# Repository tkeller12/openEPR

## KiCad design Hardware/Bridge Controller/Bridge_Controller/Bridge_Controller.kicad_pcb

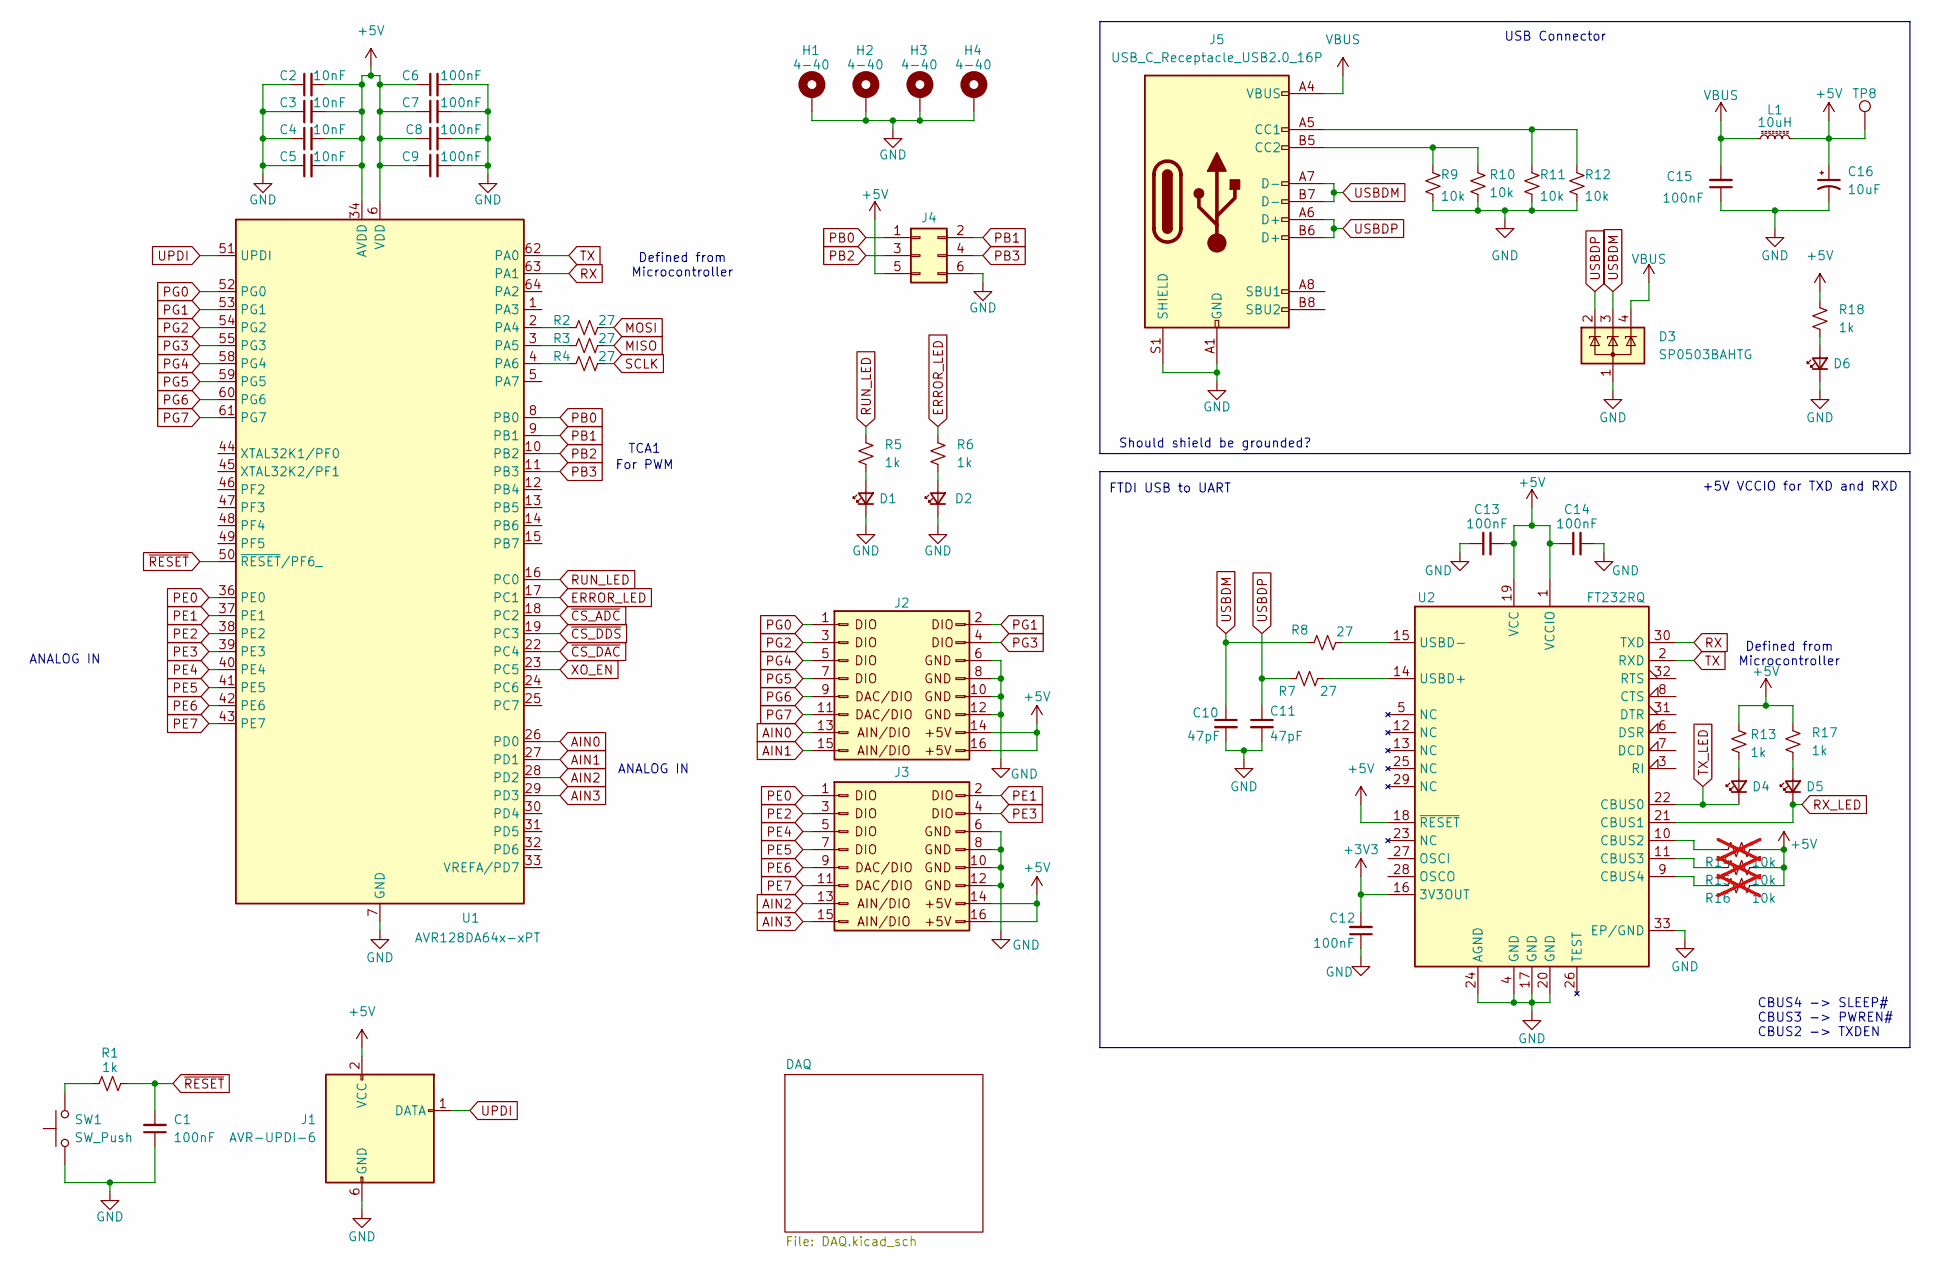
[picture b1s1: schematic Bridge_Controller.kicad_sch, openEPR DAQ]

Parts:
C1, C6, C7, C8, C9, C12, C13, C14, C15: 100nF; C_0603_1608Metric; Digikey 490-4779-1-ND
C2, C3, C4, C5: 10nF; C_0603_1608Metric; Digikey 490-4778-1-ND
C10, C11: 47pF; C_0603_1608Metric; Digikey 490-4944-1-ND
C16: 10uF; CP_EIA-3216-18_Kemet-A; Digikey 399-3684-1-ND
D1, D4, D5, D6: 150080VS75000; LED_0805_2012Metric; Digikey 732-4986-1-ND
D2: 150080SS75000; LED_0805_2012Metric; Digikey 732-4985-1-ND
D3: SP0503BAHTG; SOT-143; Digikey F2715CT-ND
H1, H2, H3, H4: 4-40; 4-40_Hole_Pad
J1: AVR-UPDI-6; PinHeader_2x03_P2.54mm_Vertical; Digikey 609-3234-ND
J2, J3: Conn_02x08_standard_header_for_IO; IDC-Header_2x08_P2.54mm_Vertical; Digikey 900-0702461602-ND
J4: PWM; PinHeader_2x03_P2.54mm_Vertical; Digikey 609-3234-ND
J5: USB_C_Receptacle_USB2.0_16P; USB_C_Receptacle_GCT_USB4085; Digikey 2073-USB4085-GF-ACT-ND
L1: 10uH; L_0805_2012Metric; Digikey 445-6762-1-ND
R1, R5, R6, R13, R17, R18: 1k; R_0603_1608Metric; Digikey 311-1.00KHRCT-ND
R2, R3, R4, R7, R8: 27; R_0603_1608Metric; Digikey 311-27GRCT-ND
R9, R10, R11, R12: 10k; R_0603_1608Metric; Digikey 311-10.0KHRCT-ND
R14, R15, R16: 10k; R_0603_1608Metric; Digikey 311-10.0KHRCT-ND; not fitted
SW1: SW_Push; SW_SPST_B3SL-1002P; Digikey SW1203CT-ND
TP8: TestPoint; TestPoint_Pad_D1.0mm
U1: AVR128DA64x-xPT; TQFP-64_10x10mm_P0.5mm; Digikey 150-AVR128DA64T-I/PTCT-ND
U2: FT232RQ; QFN-32-1EP_5x5mm_P0.5mm_EP3.1x3.1mm; Digikey 768-1307-ND

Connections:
+3V3: C12.2, U2.16 (3V3OUT)
+5V: C2.2, C3.2, C4.2, C5.2, C6.1, C7.1, C8.1, C9.1, C13.2, C14.1, C16.1, J1.2 (VCC), J2.14, J2.16, J3.14, J3.16, J4.5, L1.2, R13.1, R14.2, R15.2, R16.2, R17.1, R18.1, TP8.1, U1.6 (VDD), U1.20 (VDD), U1.34 (AVDD), U1.56 (VDD), U2.1 (VCCIO), U2.18 (~RESET), U2.19 (VCC); also elsewhere on the board
AIN0: J2.13, U1.26 (PD0)
AIN1: J2.15, U1.27 (PD1)
AIN2: J3.13, U1.28 (PD2)
AIN3: J3.15, U1.29 (PD3)
ERROR_LED: R6.1, U1.17 (PC1)
GND: C1.1, C2.1, C3.1, C4.1, C5.1, C6.2, C7.2, C8.2, C9.2, C10.2, C11.2, C12.1, C13.1, C14.2, C15.1, C16.2, D1.1 (K), D2.1 (K), D3.1 (A), D6.1 (K), H1.1, H2.1, H3.1, H4.1, J1.6 (GND), J2.6, J2.8, J2.10, J2.12, J3.6, J3.8, J3.10, J3.12, J4.6, J5.A1 (GND), J5.A12 (GND), J5.B1 (GND), J5.B12 (GND), J5.S1 (SHIELD), R9.2, R10.2, R11.2, R12.2, SW1.1, U1.7 (GND), U1.21 (GND), U1.35 (GND), U1.57 (GND), U2.4 (GND), U2.17 (GND), U2.20 (GND), U2.24 (AGND), U2.33 (EP/GND); also elsewhere on the board
MISO: R3.2; also elsewhere on the board
MOSI: R2.2; also elsewhere on the board
unnamed: D1.2 (A), R5.2
unnamed: D2.2 (A), R6.2
unnamed: D4.2 (A), R13.2
unnamed: D5.2 (A), R17.2
unnamed: D6.2 (A), R18.2
unnamed: J5.A5 (CC1), R11.1, R12.1
unnamed: J5.B5 (CC2), R9.1, R10.1
unnamed: R1.1, SW1.2
unnamed: R2.1, U1.2 (PA4)
unnamed: R3.1, U1.3 (PA5)
unnamed: R4.1, U1.4 (PA6)
unnamed: R14.1, U2.10 (CBUS2)
unnamed: R15.1, U2.11 (CBUS3)
unnamed: R16.1, U2.9 (CBUS4)
unnamed: R7.2, U2.14 (USBD+)
unnamed: R8.2, U2.15 (USBD-)
PB0: J4.1, U1.8 (PB0)
PB1: J4.2, U1.9 (PB1)
PB2: J4.3, U1.10 (PB2)
PB3: J4.4, U1.11 (PB3)
PE0: J3.1, U1.36 (PE0)
PE1: J3.2, U1.37 (PE1)
PE2: J3.3, U1.38 (PE2)
PE3: J3.4, U1.39 (PE3)
PE4: J3.5, U1.40 (PE4)
PE5: J3.7, U1.41 (PE5)
PE6: J3.9, U1.42 (PE6)
PE7: J3.11, U1.43 (PE7)
PG0: J2.1, U1.52 (PG0)
PG1: J2.2, U1.53 (PG1)
PG2: J2.3, U1.54 (PG2)
PG3: J2.4, U1.55 (PG3)
PG4: J2.5, U1.58 (PG4)
PG5: J2.7, U1.59 (PG5)
PG6: J2.9, U1.60 (PG6)
PG7: J2.11, U1.61 (PG7)
RUN_LED: R5.1, U1.16 (PC0)
RX: U1.63 (PA1), U2.30 (TXD)
RX_LED: D5.1 (K), U2.21 (CBUS1)
SCLK: R4.2; also elsewhere on the board
TX: U1.62 (PA0), U2.2 (RXD)
TX_LED: D4.1 (K), U2.22 (CBUS0)
UPDI: J1.1 (DATA), U1.51 (UPDI)
USBDM: C10.1, D3.3 (K), J5.A7 (D-), J5.B7 (D-), R8.1
USBDP: C11.1, D3.2 (K), J5.A6 (D+), J5.B6 (D+), R7.1
VBUS: C15.2, D3.4 (K), J5.A4 (VBUS), J5.A9 (VBUS), J5.B4 (VBUS), J5.B9 (VBUS), L1.1
XO_EN: U1.23 (PC5); also elsewhere on the board
~CS_ADC: U1.18 (PC2); also elsewhere on the board
~CS_DAC: U1.22 (PC4); also elsewhere on the board
~CS_DDS: U1.19 (PC3); also elsewhere on the board
~RESET: C1.2, R1.2, U1.50 (~RESET/PF6_)

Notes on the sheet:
FTDI USB to UART
ANALOG IN
TCA1
Should shield be grounded?
USB Connector
Defined from Microcontroller
CBUS4 -> SLEEP# CBUS3 -> PWREN# CBUS2 -> TXDEN
+5V VCCIO for TXD and RXD
For PWM

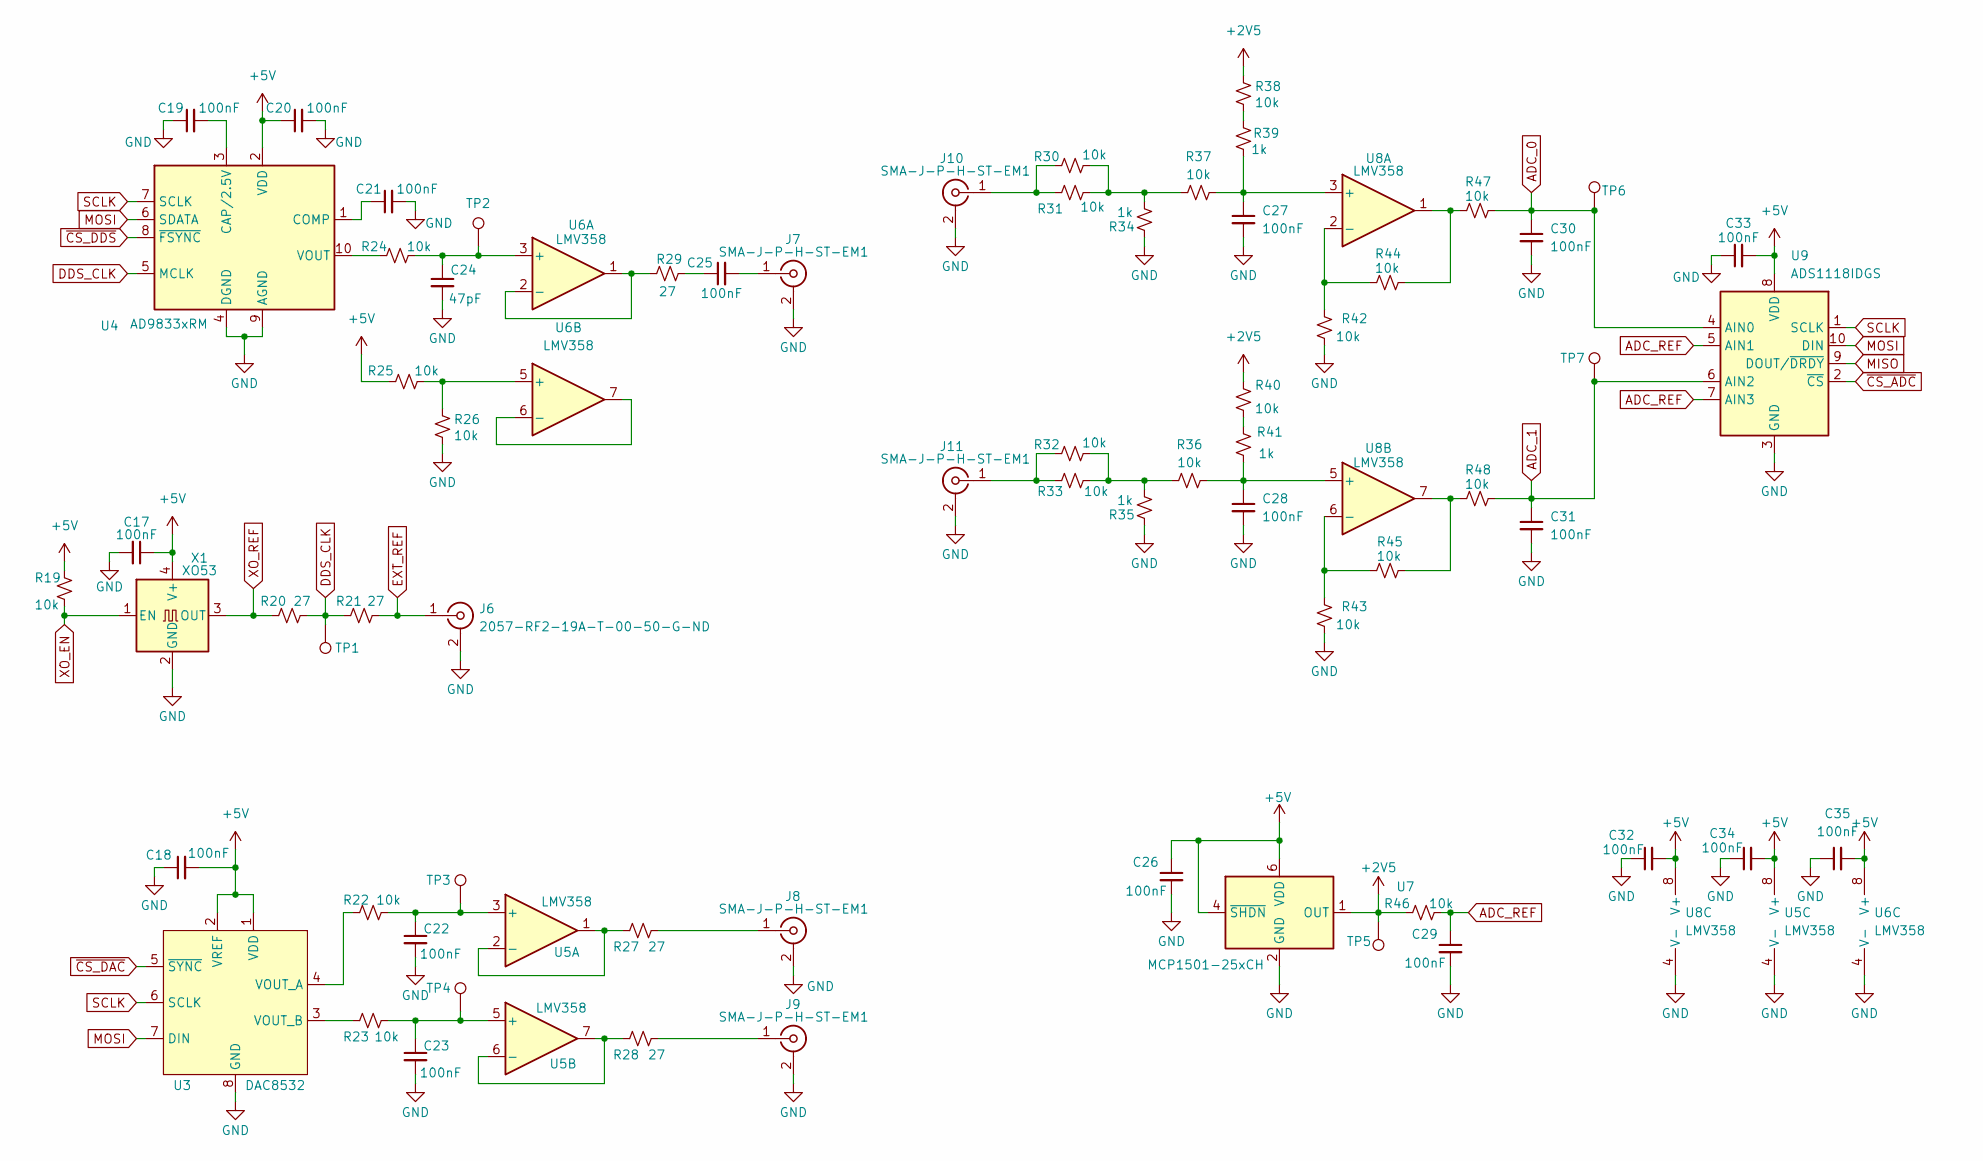
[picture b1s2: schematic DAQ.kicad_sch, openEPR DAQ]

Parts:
C17, C18, C19, C20, C21, C22, C23, C25, C26, C27, C28, C29, C30, C31, C32, C33, C34, C35: 100nF; C_0603_1608Metric; Digikey 490-4779-1-ND
C24: 47pF; C_0603_1608Metric; Digikey 490-4944-1-ND
J6: 2057-RF2-19A-T-00-50-G-ND; SMA_Amphenol_132291_Vertical; Digikey 2057-RF2-19A-T-00-50-G-ND
J7, J8, J9, J10, J11: SMA-J-P-H-ST-EM1; SMA_Samtec_SMA-J-P-X-ST-EM1_EdgeMount; Digikey SAM8857-ND
R19, R22, R23, R24, R25, R26, R30, R31, R32, R33, R36, R37, R38, R40, R42, R43, R44, R45, R46, R47, R48: 10k; R_0603_1608Metric; Digikey 311-10.0KHRCT-ND
R20, R21, R27, R28, R29: 27; R_0603_1608Metric; Digikey 311-27GRCT-ND
R34, R35, R39, R41: 1k; R_0603_1608Metric; Digikey 311-1.00KHRCT-ND
TP1, TP2, TP3, TP4, TP5, TP6, TP7: TestPoint; TestPoint_Pad_D1.0mm
U3: DAC8532; VSSOP-8_3.0x3.0mm_P0.65mm; Digikey 296-41240-1-ND
U4: AD9833xRM; MSOP-10_3x3mm_P0.5mm; Digikey 505-AD9833BRMZ-ND
U5, U6, U8: LMV358; VSSOP-8_3.0x3.0mm_P0.65mm; Digikey 296-18457-1-ND
U7: MCP1501-25xCH; SOT-23-6; Digikey MCP1501T-25E/CHYCT-ND
U9: ADS1118IDGS; VSSOP-10_3x3mm_P0.5mm; Digikey 296-38850-1-ND
X1: XO53; Oscillator_SMD_EuroQuartz_XO53-4Pin_5.0x3.2mm; Digikey XC1902CT-ND

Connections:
+2V5: R38.2, R40.2, R46.2, TP5.1, U7.1 (OUT)
+5V: C17.1, C18.2, C20.1, C26.1, C32.2, C33.2, C34.2, C35.2, R19.2, R25.1, U3.1 (VDD), U3.2 (VREF), U4.2 (VDD), U5.8 (V+), U6.8 (V+), U7.4 (~SHDN), U7.6 (VDD), U8.8 (V+), U9.8 (VDD), X1.4 (V+); also elsewhere on the board
ADC_0: C30.1, R47.1, TP6.1, U9.4 (AIN0)
ADC_1: C31.1, R48.1, TP7.1, U9.6 (AIN2)
ADC_REF: C29.1, R46.1, U9.5 (AIN1), U9.7 (AIN3)
DDS_CLK: R20.2, R21.2, TP1.1, U4.5 (MCLK)
EXT_REF: J6.1 (In), R21.1
GND: C17.2, C18.1, C19.1, C20.2, C21.2, C22.2, C23.2, C24.2, C26.2, C27.2, C28.2, C29.2, C30.2, C31.2, C32.1, C33.1, C34.1, C35.1, J6.2 (Ext), J7.2 (Ext), J8.2 (Ext), J9.2 (Ext), J10.2 (Ext), J11.2 (Ext), R26.1, R34.2, R35.2, R42.1, R43.1, U3.8 (GND), U4.4 (DGND), U4.9 (AGND), U5.4 (V-), U6.4 (V-), U7.2 (GND), U7.3 (GND), U7.5 (GND), U8.4 (V-), U9.3 (GND), X1.2 (GND); also elsewhere on the board
MISO: U9.9 (DOUT/~DRDY); also elsewhere on the board
MOSI: U3.7 (DIN), U4.6 (SDATA), U9.10 (DIN); also elsewhere on the board
unnamed: C25.1, R29.1
unnamed: C25.2, J7.1 (In)
unnamed: J8.1 (In), R27.2
unnamed: J9.1 (In), R28.2
unnamed: J10.1 (In), R30.1, R31.1
unnamed: J11.1 (In), R32.1, R33.1
unnamed: R30.2, R31.2, R34.1, R37.1
unnamed: R32.2, R33.2, R35.1, R36.1
unnamed: R38.1, R39.2
unnamed: R40.1, R41.1
unnamed: R44.1, R47.2, U8.1
unnamed: R45.1, R48.2, U8.7
unnamed: R22.1, U3.4 (VOUT_A)
unnamed: R23.1, U3.3 (VOUT_B)
unnamed: C19.2, U4.3 (CAP/2.5V)
unnamed: C21.1, U4.1 (COMP)
unnamed: R24.1, U4.10 (VOUT)
unnamed: C22.1, R22.2, TP3.1, U5.3 (+)
unnamed: R27.1, U5.1, U5.2 (-)
unnamed: C23.1, R23.2, TP4.1, U5.5 (+)
unnamed: R28.1, U5.6 (-), U5.7
unnamed: C24.1, R24.2, TP2.1, U6.3 (+)
unnamed: R29.2, U6.1, U6.2 (-)
unnamed: R25.2, R26.2, U6.5 (+)
unnamed: U6.6 (-), U6.7
unnamed: C27.1, R37.2, R39.1, U8.3 (+)
unnamed: R42.2, R44.2, U8.2 (-)
unnamed: C28.1, R36.2, R41.2, U8.5 (+)
unnamed: R43.2, R45.2, U8.6 (-)
SCLK: U3.6 (SCLK), U4.7 (SCLK), U9.1 (SCLK); also elsewhere on the board
XO_EN: R19.1, X1.1 (EN); also elsewhere on the board
XO_REF: R20.1, X1.3 (OUT)
~CS_ADC: U9.2 (~CS); also elsewhere on the board
~CS_DAC: U3.5 (~SYNC); also elsewhere on the board
~CS_DDS: U4.8 (~FSYNC); also elsewhere on the board

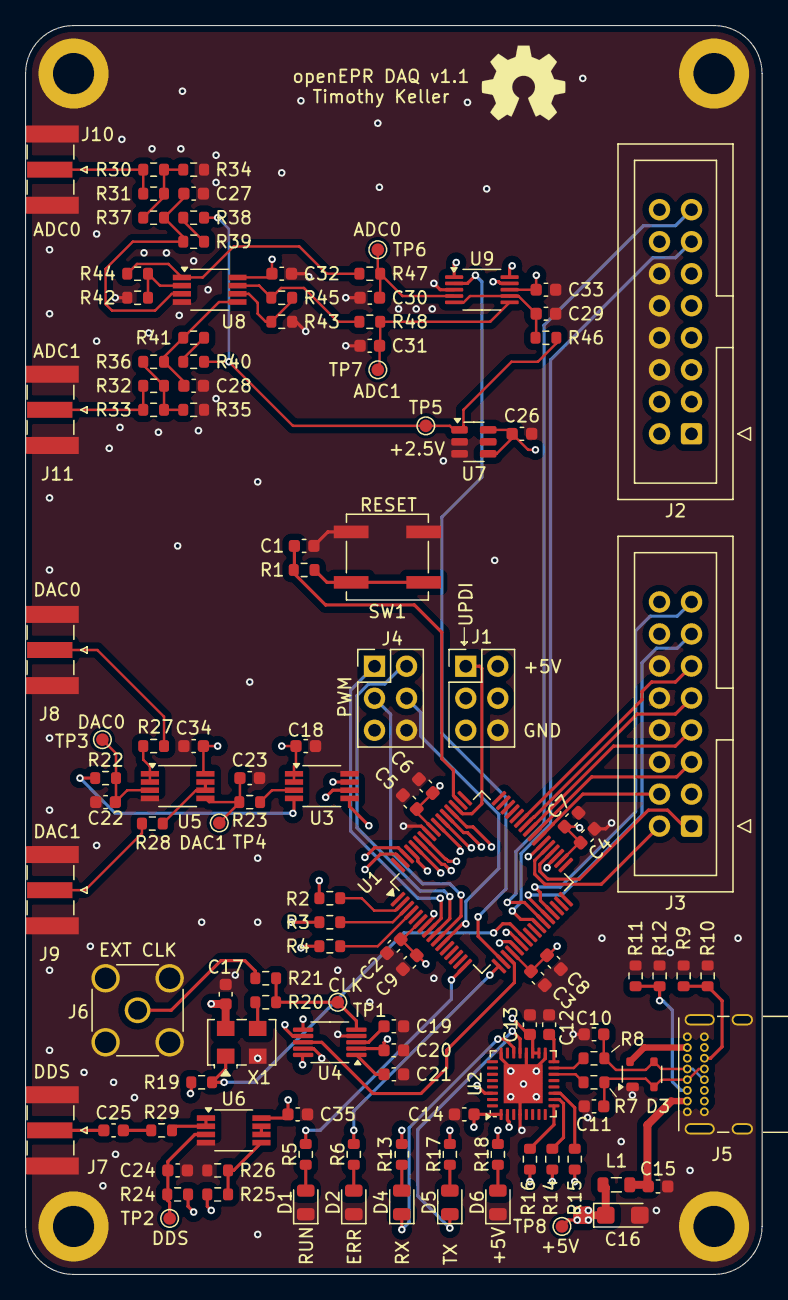
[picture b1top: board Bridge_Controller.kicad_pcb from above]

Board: 4 copper layers, 58.4 x 99.1 mm, 124 parts (0 on the bottom side), 97 nets.

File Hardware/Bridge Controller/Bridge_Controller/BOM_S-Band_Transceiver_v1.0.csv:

"Reference","Value","Footprint","Qty","DNP","Digikey"
"C1,C6,C7,C8,C9,C12,C13,C14,C15,C17,C18,C19,C20,C21,C22,C23,C25,C26,C27,C28,C29,C30,C31,C32,C33,C34,C35","100nF","Capacitor_SMD:C_0603_1608Metric","27","","490-4779-1-ND"
"C2,C3,C4,C5","10nF","Capacitor_SMD:C_0603_1608Metric","4","","490-4778-1-ND"
"C10,C11,C24","47pF","Capacitor_SMD:C_0603_1608Metric","3","","490-4944-1-ND"
"C16","10uF","Capacitor_Tantalum_SMD:CP_EIA-3216-18_Kemet-A","1","","399-3684-1-ND"
"D1,D4,D5,D6","150080VS75000","LED_SMD:LED_0805_2012Metric","4","","732-4986-1-ND"
"D2","150080SS75000","LED_SMD:LED_0805_2012Metric","1","","732-4985-1-ND"
"D3","SP0503BAHTG","Package_TO_SOT_SMD:SOT-143","1","","F2715CT-ND"
"J1","AVR-UPDI-6","Connector_PinHeader_2.54mm:PinHeader_2x03_P2.54mm_Vertical","1","","609-3234-ND"
"J2,J3","Conn_02x08_standard_header_for_IO","Connector_IDC:IDC-Header_2x08_P2.54mm_Vertical","2","","900-0702461602-ND"
"J4","PWM","Connector_PinHeader_2.54mm:PinHeader_2x03_P2.54mm_Vertical","1","","609-3234-ND"
"J5","USB_C_Receptacle_USB2.0_16P","Connector_USB:USB_C_Receptacle_GCT_USB4085","1","","2073-USB4085-GF-ACT-ND"
"J6","2057-RF2-19A-T-00-50-G-ND","Connector_Coaxial:SMA_Amphenol_132291_Vertical","1","","2057-RF2-19A-T-00-50-G-ND"
"J7,J8,J9,J10,J11","SMA-J-P-H-ST-EM1","Connector_Coaxial:SMA_Samtec_SMA-J-P-X-ST-EM1_EdgeMount","5","","SAM8857-ND"
"L1","10uH","Inductor_SMD:L_0805_2012Metric","1","","445-6762-1-ND"
"R1,R5,R6,R13,R17,R18,R34,R35,R39,R41","1k","Resistor_SMD:R_0603_1608Metric","10","","311-1.00KHRCT-ND"
"R2,R3,R4,R7,R8,R20,R21,R27,R28,R29","27","Resistor_SMD:R_0603_1608Metric","10","","311-27GRCT-ND"
"R9,R10,R11,R12,R19,R22,R23,R24,R25,R26,R30,R31,R32,R33,R36,R37,R38,R40,R42,R43,R44,R45,R46,R47,R48","10k","Resistor_SMD:R_0603_1608Metric","25","","311-10.0KHRCT-ND"
"R14,R15,R16","10k","Resistor_SMD:R_0603_1608Metric","3","DNP","311-10.0KHRCT-ND"
"SW1","SW_Push","Button_Switch_SMD:SW_SPST_B3SL-1002P","1","","SW1203CT-ND"
"U1","AVR128DA64x-xPT","Package_QFP:TQFP-64_10x10mm_P0.5mm","1","","150-AVR128DA64T-I/PTCT-ND"
"U2","FT232RQ","Package_DFN_QFN:QFN-32-1EP_5x5mm_P0.5mm_EP3.1x3.1mm","1","","768-1307-ND"
"U3","DAC8532","Package_SO:VSSOP-8_3.0x3.0mm_P0.65mm","1","","296-41240-1-ND"
"U4","AD9833xRM","Package_SO:MSOP-10_3x3mm_P0.5mm","1","","505-AD9833BRMZ-ND"
"U5,U6,U8","LMV358","Package_SO:VSSOP-8_3.0x3.0mm_P0.65mm","3","","296-18457-1-ND"
"U7","MCP1501-25xCH","Package_TO_SOT_SMD:SOT-23-6","1","","MCP1501T-25E/CHYCT-ND"
"U9","ADS1118IDGS","Package_SO:VSSOP-10_3x3mm_P0.5mm","1","","296-38850-1-ND"
"X1","XO53","Oscillator:Oscillator_SMD_EuroQuartz_XO53-4Pin_5.0x3.2mm","1","","XC1902CT-ND"

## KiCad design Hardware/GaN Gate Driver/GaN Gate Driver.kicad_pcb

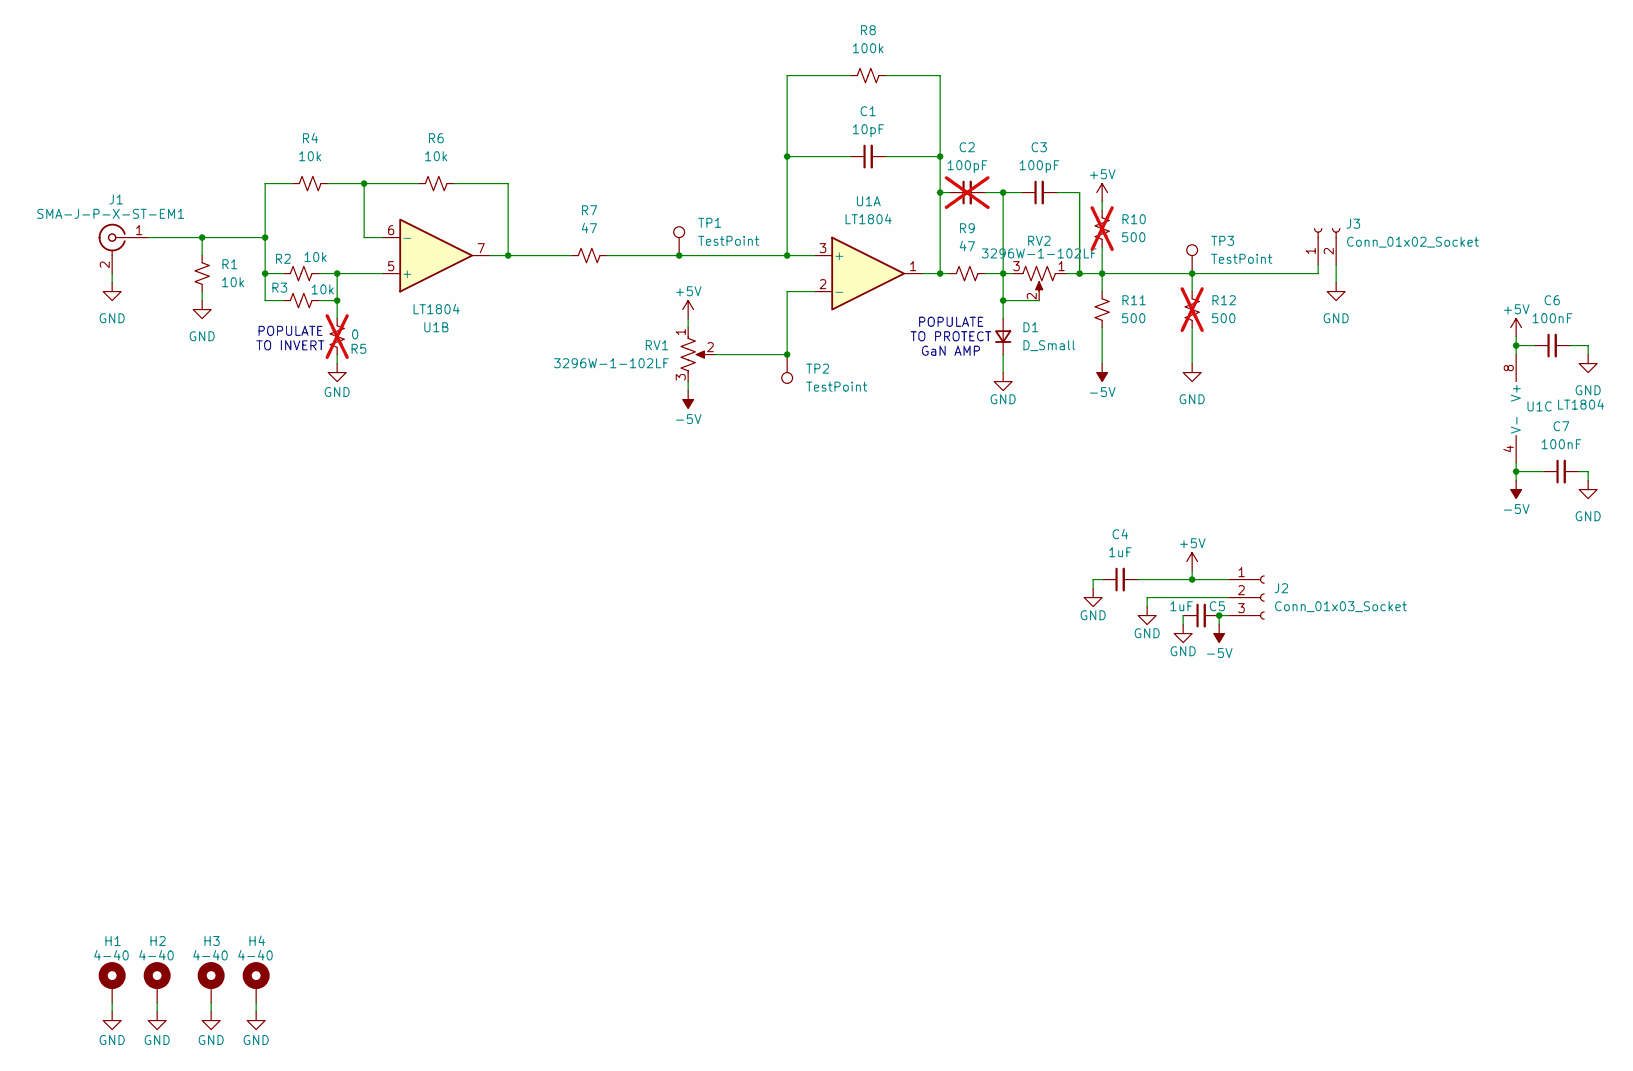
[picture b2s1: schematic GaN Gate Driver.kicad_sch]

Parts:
C1: 10pF; C_0805_2012Metric
C2: 100pF; C_0805_2012Metric; not fitted
C3: 100pF; C_0805_2012Metric
C4, C5: 1uF; C_0805_2012Metric
C6, C7: 100nF; C_0805_2012Metric
D1: D_Small; D_SOD-123
H1, H2, H3, H4: 4-40; 4-40_Hole_Pad
J1: SMA-J-P-X-ST-EM1; SMA_Samtec_SMA-J-P-X-ST-EM1_EdgeMount
J2: Conn_01x03_Socket; PinSocket_1x03_P2.54mm_Vertical
J3: Conn_01x02_Socket; PinSocket_1x02_P2.54mm_Vertical
R1, R2, R3, R4, R6: 10k; R_0805_2012Metric
R5: 0; R_0805_2012Metric; not fitted
R7, R9: 47; R_0805_2012Metric
R8: 100k; R_0805_2012Metric
R10, R12: 500; R_0805_2012Metric; not fitted
R11: 500; R_0805_2012Metric
RV1, RV2: 3296W-1-102LF; Potentiometer_Bourns_3296W_Vertical
TP1, TP2, TP3: TestPoint; TestPoint_Pad_D1.0mm
U1: LT1804; SOIC-8_3.9x4.9mm_P1.27mm

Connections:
+5V: C4.2, C6.1, J2.1, R10.2, RV1.1, U1.8 (V+)
-5V: C5.2, C7.1, J2.3, R11.1, RV1.3, U1.4 (V-)
GND: C4.1, C5.1, C6.2, C7.2, D1.1 (K), H1.1, H2.1, H3.1, H4.1, J1.2 (Ext), J2.2, J3.2, R1.1, R5.1, R12.1
unnamed: C1.2, C2.1, R8.2, R9.1, U1.1
unnamed: C2.2, C3.1, D1.2 (A), R9.2, RV2.2, RV2.3
unnamed: J1.1 (In), R1.2, R2.1, R3.1, R4.1
unnamed: C3.2, J3.1, R10.1, R11.2, R12.2, RV2.1, TP3.1
unnamed: R6.2, R7.1, U1.7
unnamed: C1.1, R7.2, R8.1, TP1.1, U1.3 (+)
unnamed: RV1.2, TP2.1, U1.2 (-)
unnamed: R2.2, R3.2, R5.2, U1.5 (+)
unnamed: R4.2, R6.1, U1.6 (-)

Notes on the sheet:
POPULATE TO PROTECT GaN AMP
POPULATE TO INVERT

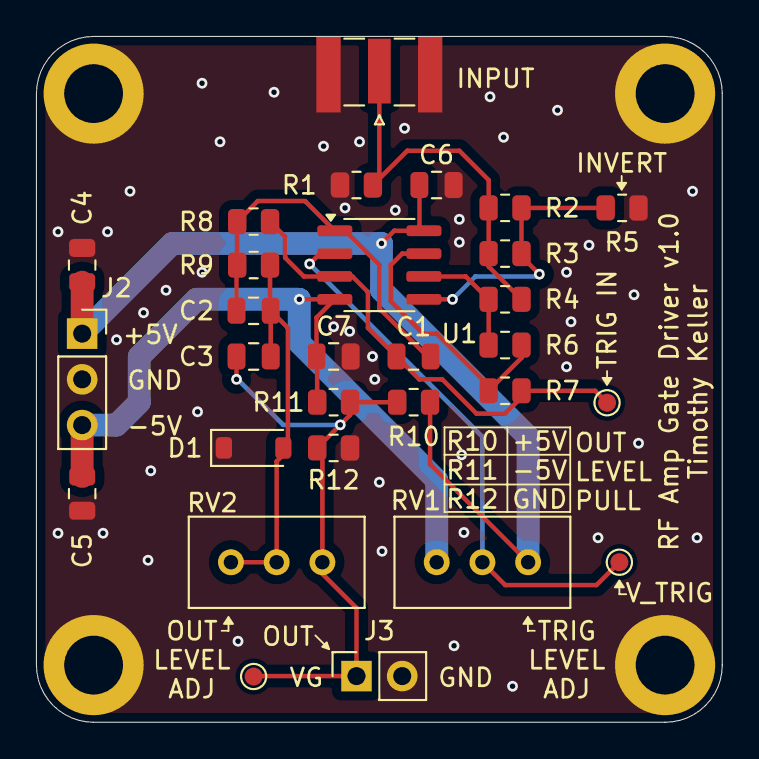
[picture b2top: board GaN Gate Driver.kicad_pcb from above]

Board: 2 copper layers, 38.1 x 38.1 mm, 33 parts (0 on the bottom side), 12 nets.

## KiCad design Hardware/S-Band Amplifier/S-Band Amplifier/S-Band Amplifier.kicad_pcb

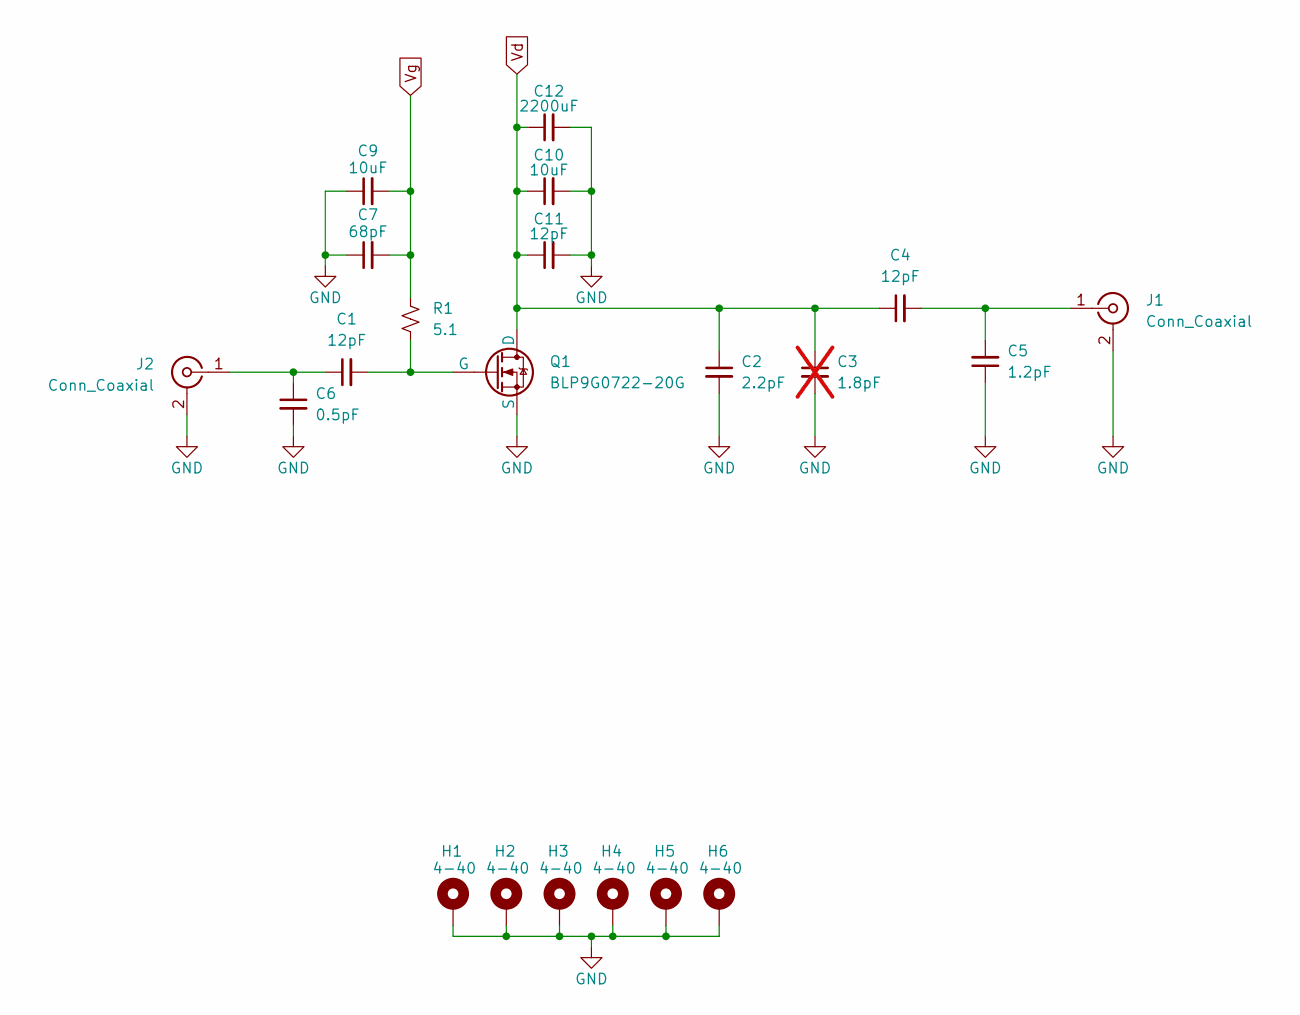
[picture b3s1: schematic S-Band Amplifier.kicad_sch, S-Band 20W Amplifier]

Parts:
C1, C4, C11: 12pF; C_0805_2012Metric
C2: 2.2pF; C_0805_2012Metric
C3: 1.8pF; C_0805_2012Metric; not fitted
C5: 1.2pF; C_0805_2012Metric
C6: 0.5pF; C_0805_2012Metric
C7: 68pF; C_0805_2012Metric
C9, C10: 10uF; C_1210_3225Metric
C12: 2200uF
H1, H2, H3, H4, H5, H6: 4-40; 4-40_Hole_Pad
J1, J2: Conn_Coaxial; SMA_Samtec_SMA-J-P-X-ST-EM1_EdgeMount
Q1: BLP9G0722-20G
R1: 5.1; R_0805_2012Metric

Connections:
GND: C2.2, C3.2, C5.1, C6.2, C7.1, C9.1, C10.2, C11.2, C12.2, H1.1, H2.1, H3.1, H4.1, H5.1, H6.1, J1.2 (Ext), J2.2 (Ext), Q1.3 (S); also elsewhere on the board
unnamed: C4.2, C5.2, J1.1 (In)
unnamed: C1.1, C6.1, J2.1 (In)
unnamed: C1.2, Q1.2 (G), R1.2
Vd: C2.1, C3.1, C4.1, C10.1, C11.1, C12.1, Q1.1 (D)
Vg: C7.2, C9.2, R1.1; also elsewhere on the board

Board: 2 copper layers, 20 parts (0 on the bottom side), 6 nets, no tracks yet.

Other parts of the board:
C8: 12pF; C_0805_2012Metric

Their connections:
GND: C8.1; also elsewhere on the board
Vg: C8.2; also elsewhere on the board

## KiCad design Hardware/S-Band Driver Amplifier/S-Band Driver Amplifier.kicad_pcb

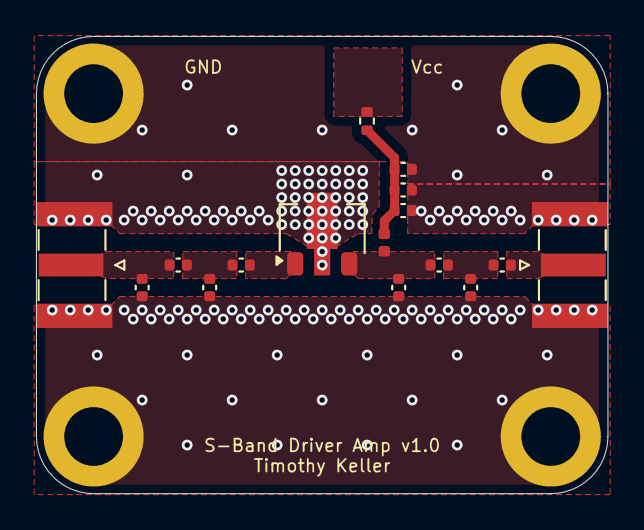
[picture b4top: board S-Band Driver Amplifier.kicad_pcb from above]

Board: 2 copper layers, 31.8 x 25.4 mm, 20 parts (0 on the bottom side), 8 nets.

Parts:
C1, C3, C8, C9: 1.3pF; C_0402_1005Metric
C2, C11: 4.7pF; C_0402_1005Metric
C4, C10: 2.7pF; C_0402_1005Metric
C5: 1nF; C_0402_1005Metric
C6: 1uF; C_0402_1005Metric
C7: 10nF; C_0402_1005Metric
H1, H2, H3, H4: 4-40; 4-40_Hole_Pad
J1, J2: Conn_Coaxial; SMA_Samtec_SMA-J-P-X-ST-EM1_EdgeMount
L1: 8.7nH; L_0402_1005Metric
R1: 0; R_0402_1005Metric
U1: SKY65162-70LF; SOT-89-3

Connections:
GND: C3.1, C4.1, C5.2, C6.2, C7.2, C9.1, C10.1, H1.1, H2.1, H3.1, H4.1, J1.2 (Ext), J2.2 (Ext), U1.2 (GND)
unnamed: C1.2, C3.2, C8.1
unnamed: C2.1, C4.2, L1.2, U1.3
unnamed: C5.1, C6.1, C7.1, L1.1, R1.2
unnamed: C8.2, U1.1
unnamed: C2.2, C10.2, C11.1
unnamed: C1.1, C9.2, J1.1 (In)
unnamed: C11.2, J2.1 (In)

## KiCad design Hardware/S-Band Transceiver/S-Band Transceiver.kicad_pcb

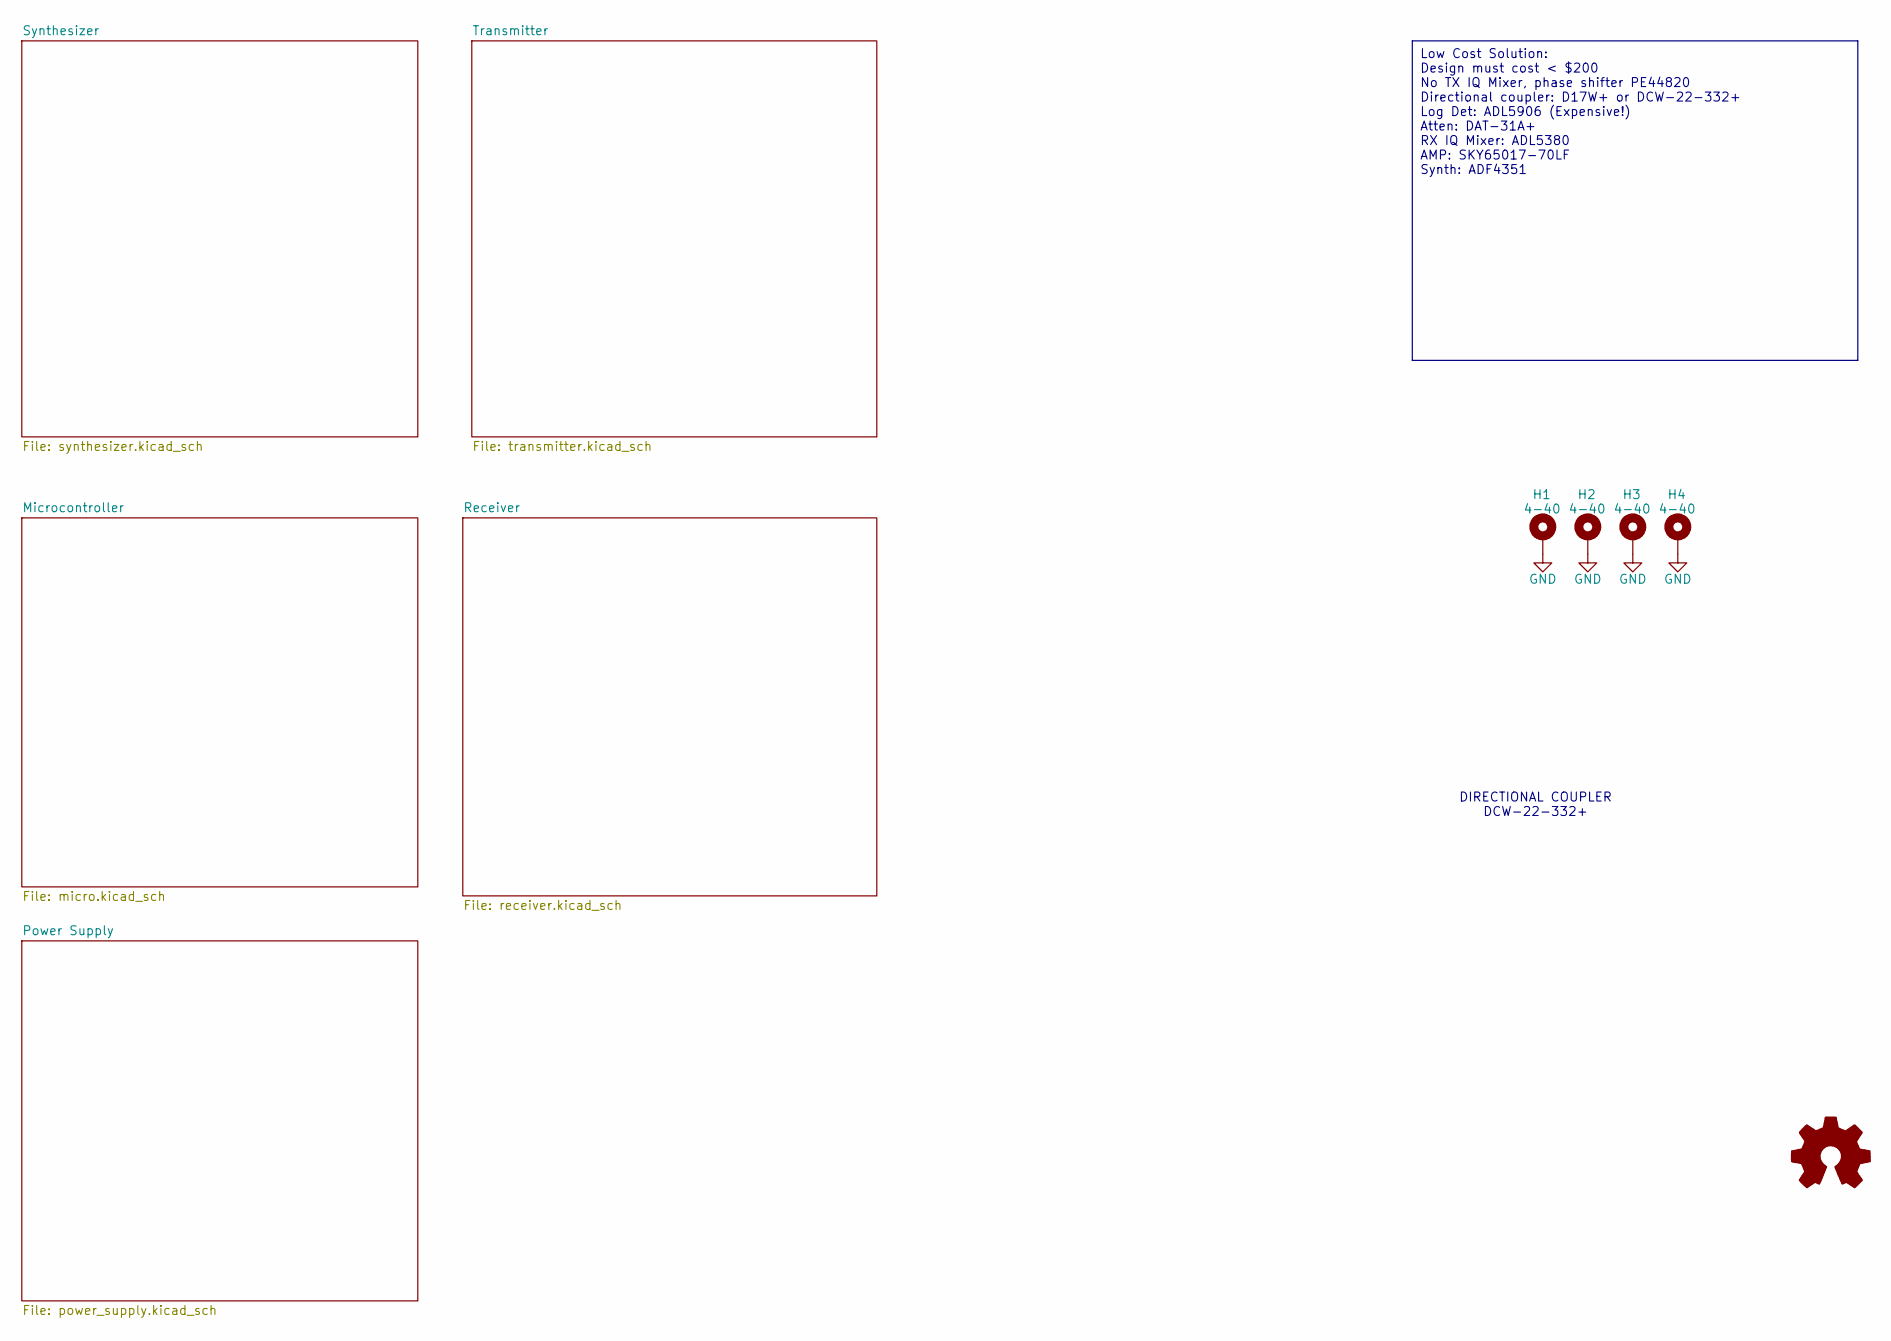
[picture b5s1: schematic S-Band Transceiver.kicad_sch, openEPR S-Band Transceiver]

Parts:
H1, H2, H3, H4: 4-40; 4-40_Hole_Pad

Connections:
GND: H1.1, H2.1, H3.1, H4.1; also elsewhere on the board

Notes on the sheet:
Low Cost Solution: Design must cost < $200 No TX IQ Mixer, phase shifter PE44820 Directional coupler: D17W+ or DCW-22-332+ Log Det: ADL5906 (Expensive!) Atten: DAT-31A+ RX IQ Mixer: ADL5380 AMP: SKY65017-70LF Synth: ADF4351
DIRECTIONAL COUPLER DCW-22-332+
